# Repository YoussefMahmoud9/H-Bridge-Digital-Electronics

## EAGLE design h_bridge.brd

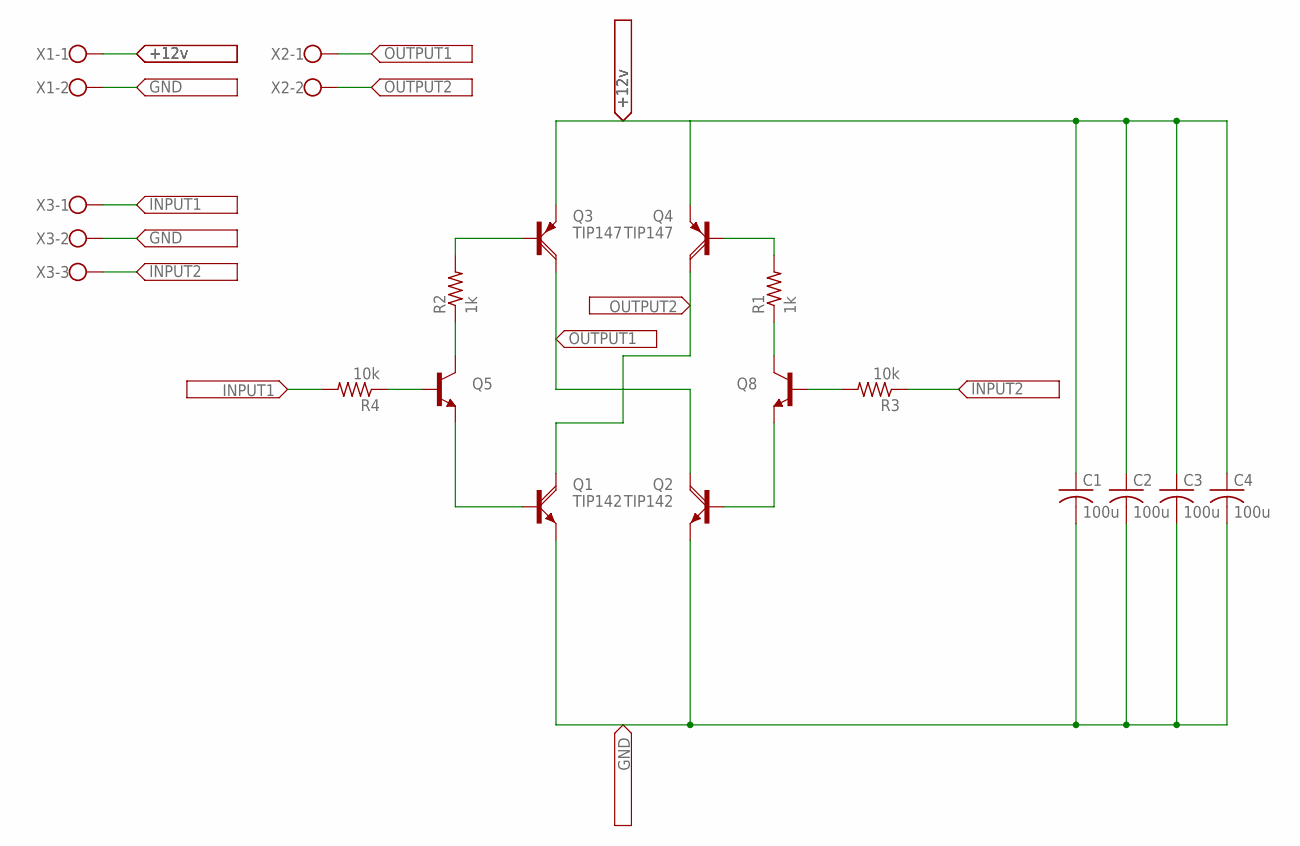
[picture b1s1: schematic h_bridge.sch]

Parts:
C1, C2, C3, C4: 100u; C025-025X050
Q1, Q2: TIP142; SOT93
Q3, Q4: TIP147; SOT93
Q5, Q8: TRANSISTOR_NPNTO92; TO-92
R1, R2: 1k; 0207/15
R3, R4: 10k; 0207/15
X1, X2: W237-02P; W237-132
X3: W237-03P; W237-133

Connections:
+12V: C1.1, C2.1, C3.1, C4.1, Q3.E, Q4.E, X1.1
GND: C1.2, C2.2, C3.2, C4.2, Q1.E, Q2.E, X1.2, X3.2
INPUT1: R4.2, X3.1
INPUT2: R3.1, X3.3
unnamed: Q5.3 (C), R2.1
unnamed: Q3.B, R2.2
unnamed: Q4.B, R1.2
unnamed: Q8.3 (C), R1.1
unnamed: Q1.B, Q5.1 (E)
unnamed: Q2.B, Q8.1 (E)
unnamed: Q5.2 (B), R4.1
unnamed: Q8.2 (B), R3.2
OUTPUT1: Q2.C, Q3.C, X2.1
OUTPUT2: Q1.C, Q4.C, X2.2

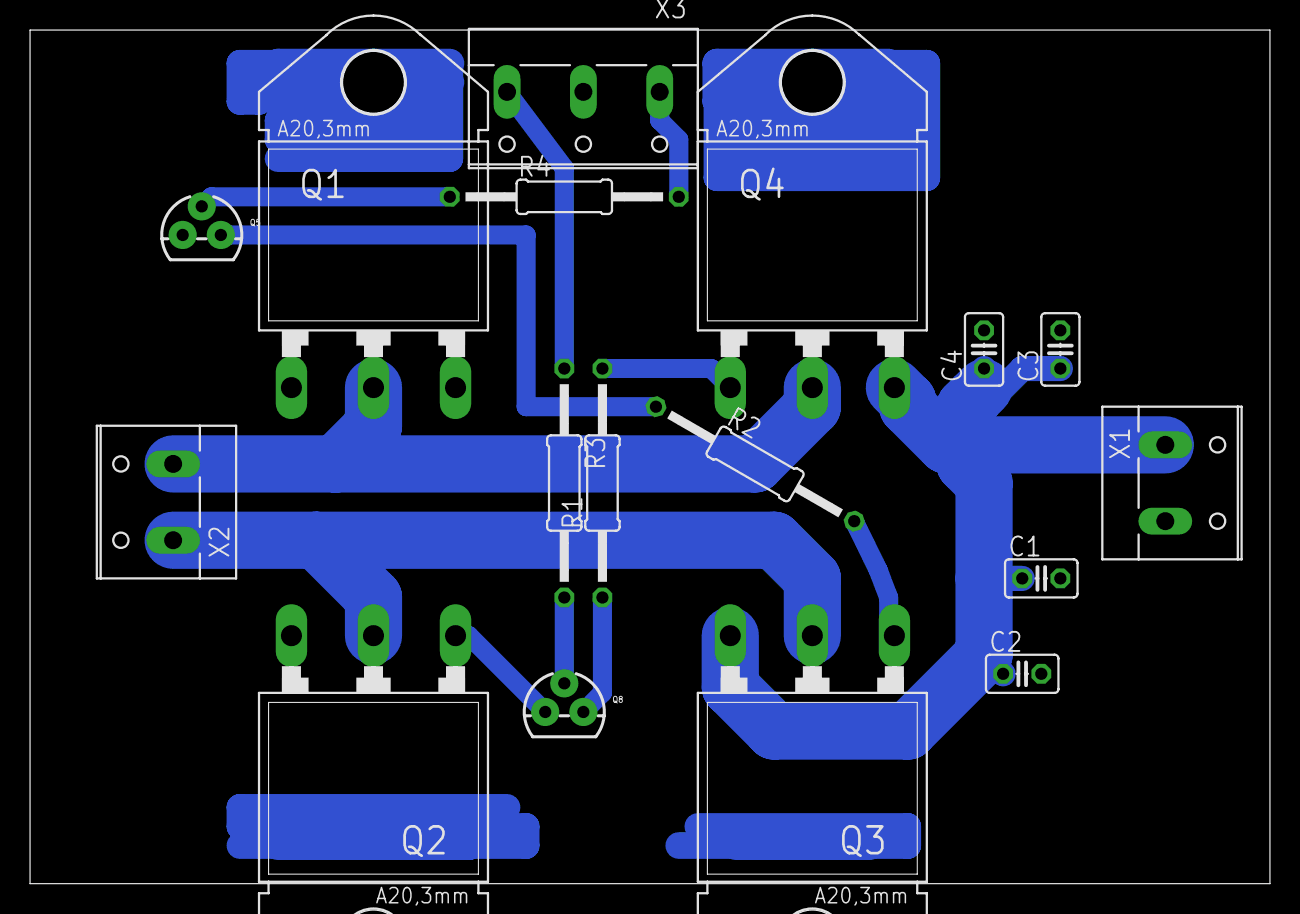
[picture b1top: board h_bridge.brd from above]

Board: 2 copper layers, 82.5 x 56.8 mm, 17 parts (0 on the bottom side), 14 nets.
